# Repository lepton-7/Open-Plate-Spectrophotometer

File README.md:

# Open-Plate-Spectrophotometer

An open-source project to build a 96-well spectrophotometer operating at 620nm. Designed from the ground-up focusing on robust electronic design. Funded by the [think[box] Student Project Fund](https://case.edu/thinkbox/funding/student-project-fund) for the 2022-2023 academic year.

## Test Prototype (v0.0.2)

This project was born out of an appreciation for [Cerillo's portable microplate reader](https://cerillo.bio/stratus-2/) and the arrogant desire to open-source it by recreating what they made on my own. I designed a limited test prototype during the summer (I think sometime in July?) before the school year restarted to see what is required to realise the idea of a small form-factor, portable plate reader.

### Concept and Schematic

#### Functional block diagram

The idea is simple: control 96-element grids of LEDs and light sensors to address individual wells in a plate, convert the signal from the light sensor into something machine parsable, then finally do some ✨math✨ to get an optical density value for each well.

#### LED and detector grids

I decided to _not_ build a full 96-capable prototype. Instead, I opted to test all the relevant units I needed on a smaller scale. The result was a prototype with all 8 rows (A-H) but only two columns.

Independent control of each element is easily achieved by connecting the grid high and low sides to control MOSFETs:

Each row was connected to +5V via p-ch FETs (yes i know, they're wired incorrectly) and each column was connected to GND via n-ch FETs. Each FET gate is assigned its own pin on the MCU to independently control individual elements.

A similar idea is used for switching inputs from specific photodiode elements.

#### Detectors: photodiodes vs phototransistors

The hard bit for a device like this taking light that passes through the sample wells and converting that into a digital signal. Initially, I planned on using [phototransistors](https://www.digikey.com/en/articles/the-basics-of-photodiodes-and-phototransistors-and-how-to-apply-them) to transform a change in incident light intensity into a change in current. But these devices are pretty imprecise and do not have the best linearity. To make phototransistors work, I would have needed to do some really careful biasing -- something I did not think I needed.

The alternative was to use photodiodes. These are a bit better in the sense that they would have required a lot fewer supporting components. They also have pretty nice characteristics:

<fig>

<figcaption>Plot from Analog ADI</figcaption>
</fig>

These devices are pretty much linear in their response to incident light intensity: A 10x increase in incident intensity results in a 10x increase in reverse current.

#### Transimpedance amplifiers and ADCs

Converting current going through a photodiode into digital information is a two-step process. This is nothing new; the typical strategy is to use a transimpedance amplifier to convert transform a current signal into a voltage signal followed by an ADC that can convert the voltage signal into a digital value:

<fig>

<figcaption>TIA diagram from wikimedia commons.</figcaption>
</fig>

The transfer function is also pretty simple for a TIA:
$$ V_{out} = -I_{in}R_f $$

This is implemented as:

<fig>

</fig>

The principle is the same, just compressed a little. The current source is replaced by the photodiode, mulit-channel opamps are used to save space, and $V_{out}$ passes through a standard Schottky diode before being connected to the ADC inputs.

I used an 8ch ADC to independently connect each row for pseudo-switching of the detector outputs. High-side p-ch FET switches control V<sub>cc</sub> for the TIAs.

<fig>

</fig>

The 12-bit ADC converts output voltage into a digital signal referenced to a stable 5V signal generated by a voltage reference amplified by a low-noise voltage follower:

<fig>

</fig>

The MCU, an arduino nano, communicates with the ADC over I<sup>2</sup>C.

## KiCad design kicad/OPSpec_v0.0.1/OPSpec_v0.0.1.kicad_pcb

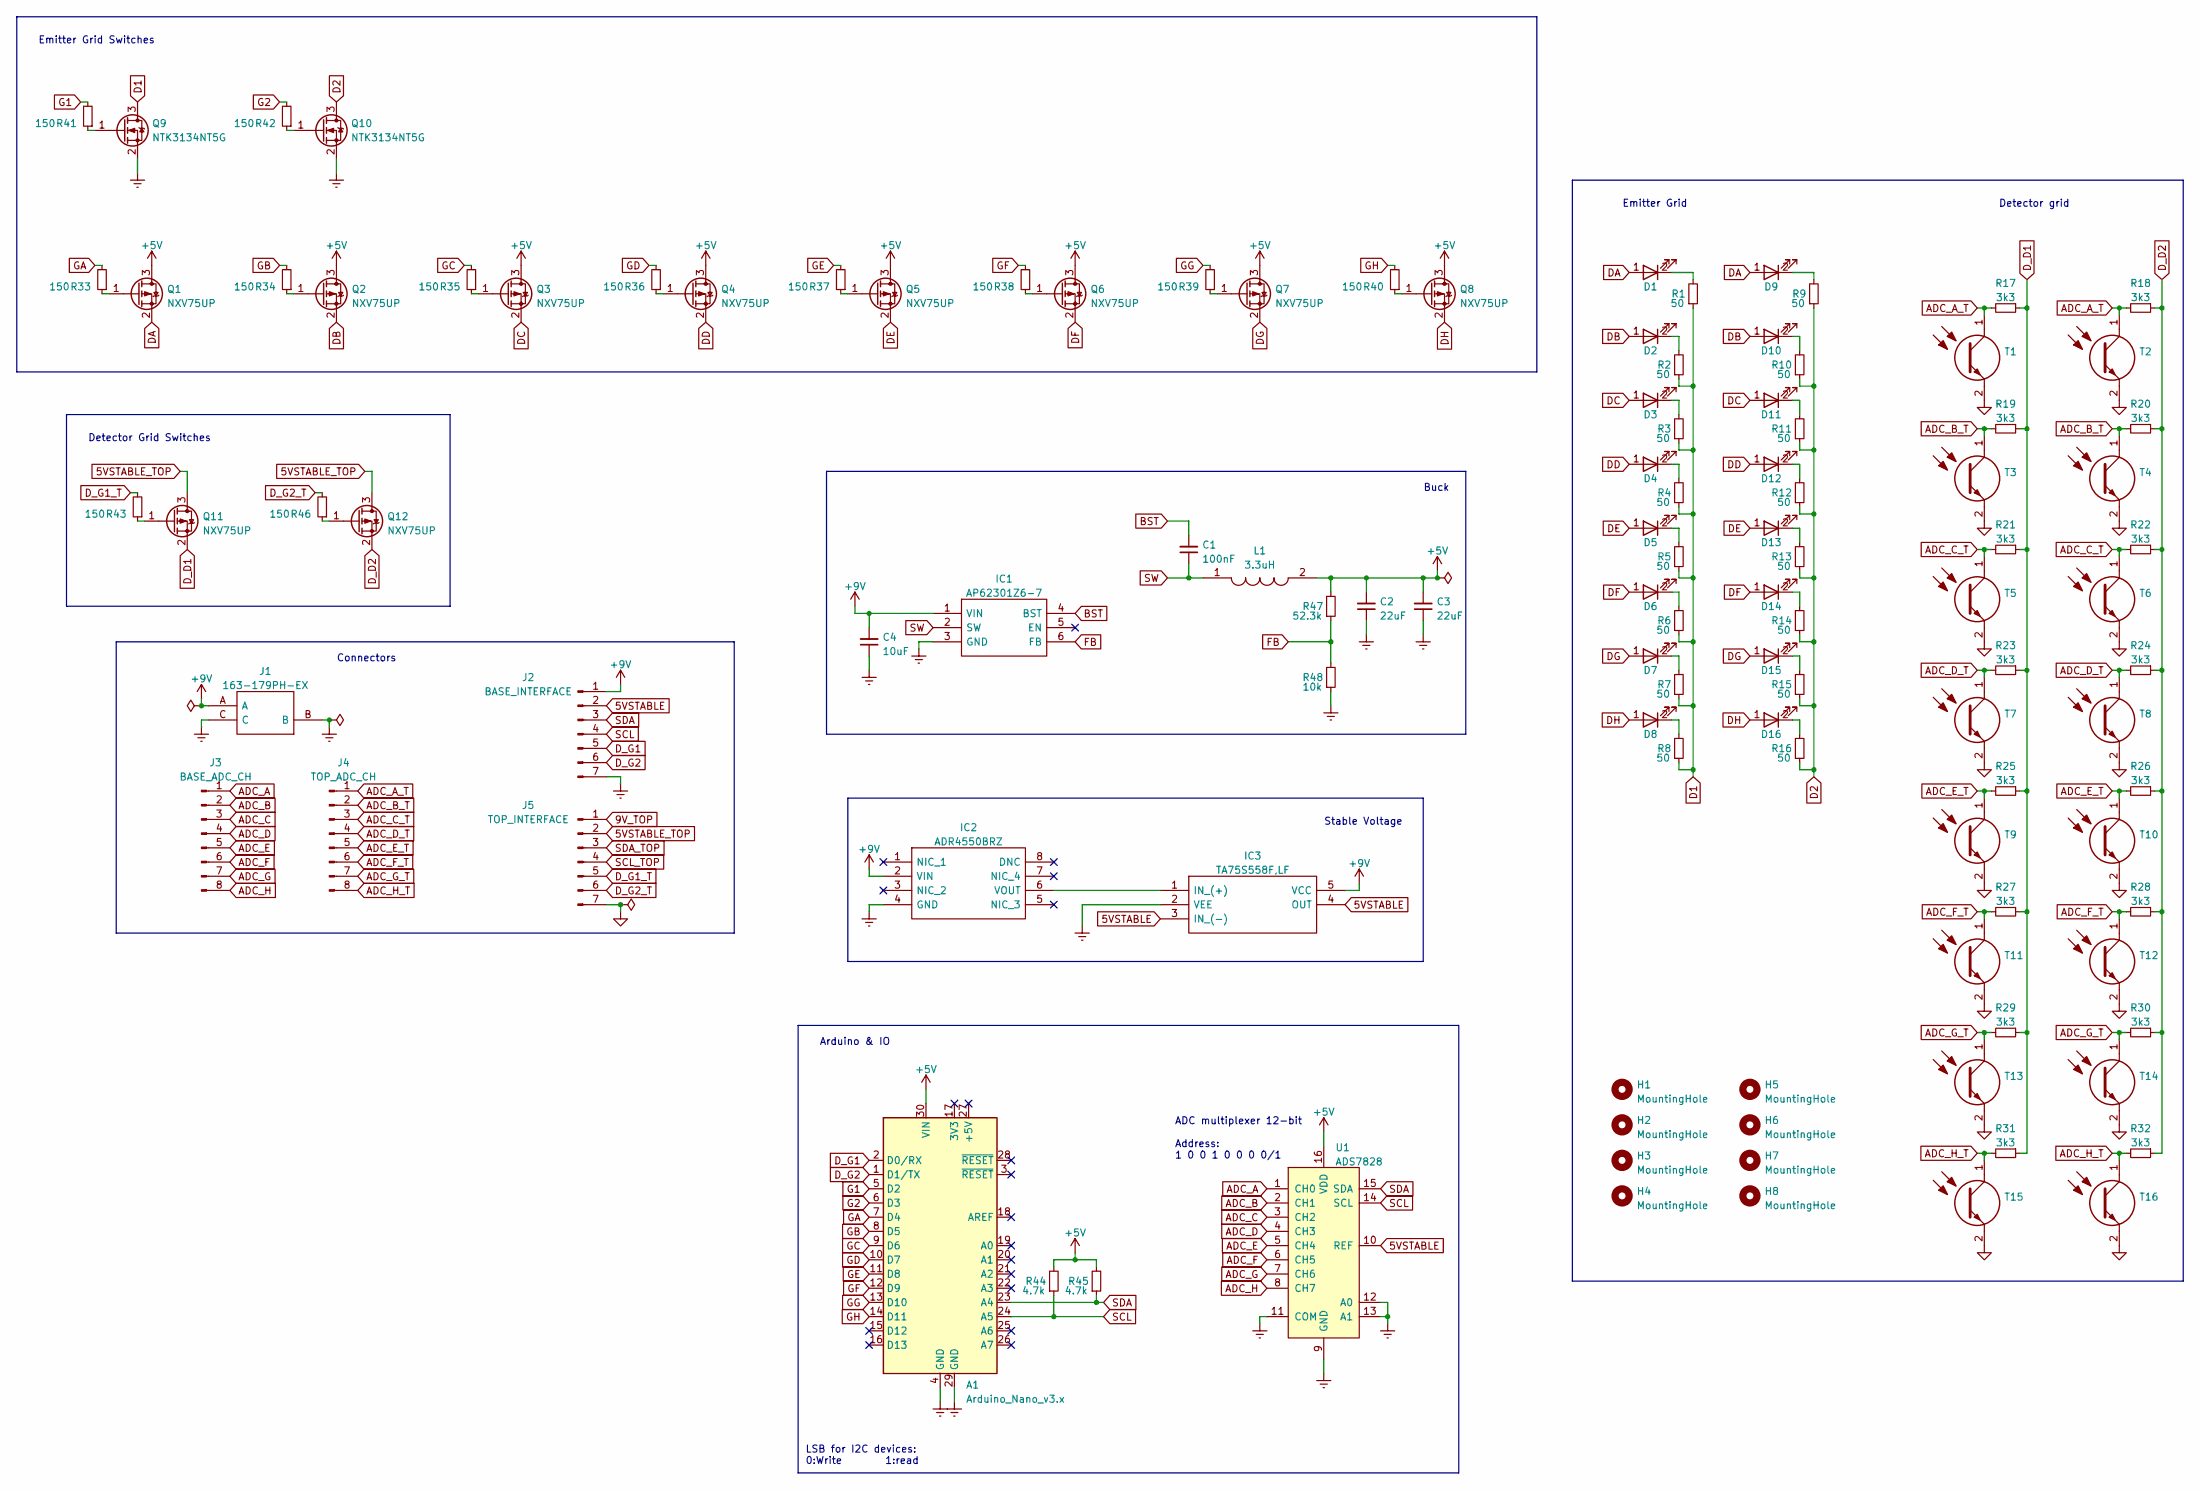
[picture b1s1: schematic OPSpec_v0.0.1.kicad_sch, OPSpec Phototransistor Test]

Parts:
A1: Arduino_Nano_v3.x; Arduino_Nano
C1: 100nF; C_0805_2012Metric
C2, C3: 22uF; C_0805_2012Metric
C4: 10uF; C_0805_2012Metric
D1, D2, D3, D4, D5, D6, D7, D8, D9, D10, D11, D12, D13, D14, D15, D16: GR_JTLPS1.23-G7H4-45-1-150-R33; GRJTLPS123G7H4451150R33; Mouser Part Number 720-GRJTLPS123A1052
H1, H2, H3, H4, H5, H6, H7, H8: MountingHole; MountingHole_2.5mm
IC1: AP62301Z6-7; SOTFL50P162X60-6N; Mouser Part Number 621-AP62301Z6-7
IC2: ADR4550BRZ; SOIC127P600X175-8N; Mouser Part Number 584-ADR4550BRZ
IC3: TA75S558F,LF; TA75S558FLF; Mouser Part Number 757-TA75S558FLF
J1: 163-179PH-EX; 163179PHEX; Mouser Part Number 163-179PH-EX
J2: BASE_INTERFACE; PinHeader_1x07_P2.54mm_Vertical
J3: BASE_ADC_CH; PinHeader_1x08_P2.54mm_Vertical
J4: TOP_ADC_CH; PinHeader_1x08_P2.54mm_Vertical
J5: TOP_INTERFACE; PinHeader_1x07_P2.54mm_Vertical
L1: 3.3uH; INDPM2016X100N; Mouser Part Number 963-MAKK2016T3R3M
Q1, Q2, Q3, Q4, Q5, Q6, Q7, Q8, Q11, Q12: NXV75UP; SOT-23
Q9, Q10: NTK3134NT5G; Mouser Part Number 863-NTK3134NT5G
R1, R2, R3, R4, R5, R6, R7, R8, R9, R10, R11, R12, R13, R14, R15, R16: 50; R_0603_1608Metric
R17, R18, R19, R20, R21, R22, R23, R24, R25, R26, R27, R28, R29, R30, R31, R32: 3k3; R_0603_1608Metric
R33, R34, R35, R36, R37, R38, R39, R40, R41, R42, R43, R46: 150; R_0603_1608Metric
R44, R45: 4.7k; R_0603_1608Metric
R47: 52.3k; R_0603_1608Metric
R48: 10k; R_0603_1608Metric
T1, T2, T3, T4, T5, T6, T7, T8, T9, T10, T11, T12, T13, T14, T15, T16: KDT00030TR; Mouser Part Number 512-KDT00030TR
U1: ADS7828; TSSOP-16_4.4x5mm_P0.65mm

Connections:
5VSTABLE: IC3.3 (IN_(-)), IC3.4 (OUT), J2.2, U1.10 (REF)
5VSTABLE_TOP: J5.2, Q11.3 (D), Q12.3 (D)
9V_TOP: J5.1
+5V: A1.30 (VIN), C2.2, C3.2, L1.2, Q1.3 (D), Q2.3 (D), Q3.3 (D), Q4.3 (D), Q5.3 (D), Q6.3 (D), Q7.3 (D), Q8.3 (D), R44.2, R45.2, R47.2, U1.16 (VDD)
+9V: C4.2, IC1.1 (VIN), IC2.2 (VIN), IC3.5 (VCC), J1.A, J2.1
ADC_A: J3.1, U1.1 (CH0)
ADC_A_T: J4.1, R17.2, R18.2, T1.1 (C), T2.1 (C)
ADC_B: J3.2, U1.2 (CH1)
ADC_B_T: J4.2, R19.2, R20.2, T3.1 (C), T4.1 (C)
ADC_C: J3.3, U1.3 (CH2)
ADC_C_T: J4.3, R21.2, R22.2, T5.1 (C), T6.1 (C)
ADC_D: J3.4, U1.4 (CH3)
ADC_D_T: J4.4, R23.2, R24.2, T7.1 (C), T8.1 (C)
ADC_E: J3.5, U1.5 (CH4)
ADC_E_T: J4.5, R25.2, R26.2, T9.1 (C), T10.1 (C)
ADC_F: J3.6, U1.6 (CH5)
ADC_F_T: J4.6, R27.2, R28.2, T11.1 (C), T12.1 (C)
ADC_G: J3.7, U1.7 (CH6)
ADC_G_T: J4.7, R29.2, R30.2, T13.1 (C), T14.1 (C)
ADC_H: J3.8, U1.8 (CH7)
ADC_H_T: J4.8, R31.2, R32.2, T15.1 (C), T16.1 (C)
BST: C1.2, IC1.4 (BST)
D1: Q9.3 (D), R1.1, R2.1, R3.1, R4.1, R5.1, R6.1, R7.1, R8.1
D2: Q10.3 (D), R9.1, R10.1, R11.1, R12.1, R13.1, R14.1, R15.1, R16.1
DA: D1.1 (A), D9.1 (A), Q1.2 (S)
DB: D2.1 (A), D10.1 (A), Q2.2 (S)
DC: D3.1 (A), D11.1 (A), Q3.2 (S)
DD: D4.1 (A), D12.1 (A), Q4.2 (S)
DE: D5.1 (A), D13.1 (A), Q5.2 (S)
DF: D6.1 (A), D14.1 (A), Q6.2 (S)
DG: D7.1 (A), D15.1 (A), Q7.2 (S)
DH: D8.1 (A), D16.1 (A), Q8.2 (S)
D_D1: Q11.2 (S), R17.1, R19.1, R21.1, R23.1, R25.1, R27.1, R29.1, R31.1
D_D2: Q12.2 (S), R18.1, R20.1, R22.1, R24.1, R26.1, R28.1, R30.1, R32.1
D_G1: A1.2 (D0/RX), J2.5
D_G1_T: J5.5, R43.2
D_G2: A1.1 (D1/TX), J2.6
D_G2_T: J5.6, R46.2
Earth: A1.4 (GND), A1.29 (GND), C2.1, C3.1, C4.1, IC1.3 (GND), IC2.4 (GND), IC3.2 (VEE), J1.B, J1.C, J2.7, Q9.2 (S), Q10.2 (S), R48.1, U1.9 (GND), U1.11 (COM), U1.12 (A0), U1.13 (A1)
FB: IC1.6 (FB), R47.1, R48.2
G1: A1.5 (D2), R41.2
G2: A1.6 (D3), R42.2
GA: A1.7 (D4), R33.2
GB: A1.8 (D5), R34.2
GC: A1.9 (D6), R35.2
GD: A1.10 (D7), R36.2
GE: A1.11 (D8), R37.2
GF: A1.12 (D9), R38.2
GG: A1.13 (D10), R39.2
GH: A1.14 (D11), R40.2
GND: J5.7, T1.2 (E), T2.2 (E), T3.2 (E), T4.2 (E), T5.2 (E), T6.2 (E), T7.2 (E), T8.2 (E), T9.2 (E), T10.2 (E), T11.2 (E), T12.2 (E), T13.2 (E), T14.2 (E), T15.2 (E), T16.2 (E)
unnamed: D1.2 (K), R1.2
unnamed: D2.2 (K), R2.2
unnamed: D3.2 (K), R3.2
unnamed: D4.2 (K), R4.2
unnamed: D5.2 (K), R5.2
unnamed: D6.2 (K), R6.2
unnamed: D7.2 (K), R7.2
unnamed: D8.2 (K), R8.2
unnamed: D9.2 (K), R9.2
unnamed: D10.2 (K), R10.2
unnamed: D11.2 (K), R11.2
unnamed: D12.2 (K), R12.2
unnamed: D13.2 (K), R13.2
unnamed: D14.2 (K), R14.2
unnamed: D15.2 (K), R15.2
unnamed: D16.2 (K), R16.2
unnamed: IC2.6 (VOUT), IC3.1 (IN_(+))
unnamed: Q1.1 (G), R33.1
unnamed: Q2.1 (G), R34.1
unnamed: Q3.1 (G), R35.1
unnamed: Q4.1 (G), R36.1
unnamed: Q5.1 (G), R37.1
unnamed: Q6.1 (G), R38.1
unnamed: Q7.1 (G), R39.1
unnamed: Q8.1 (G), R40.1
unnamed: Q9.1 (G), R41.1
unnamed: Q10.1 (G), R42.1
unnamed: Q11.1 (G), R43.1
unnamed: Q12.1 (G), R46.1
SCL: A1.24 (A5), J2.4, R44.1, U1.14 (SCL)
SCL_TOP: J5.4
SDA: A1.23 (A4), J2.3, R45.1, U1.15 (SDA)
SDA_TOP: J5.3
SW: C1.1, IC1.2 (SW), L1.1

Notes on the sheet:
ADC multiplexer 12-bit Address: 1 0 0 1 0 0 0 0/1
Arduino & IO
Connectors
Detector Grid Switches
Emitter Grid Switches
Detector grid
Buck
LSB for I2C devices: 0:Write 1:read
Emitter Grid
Stable Voltage

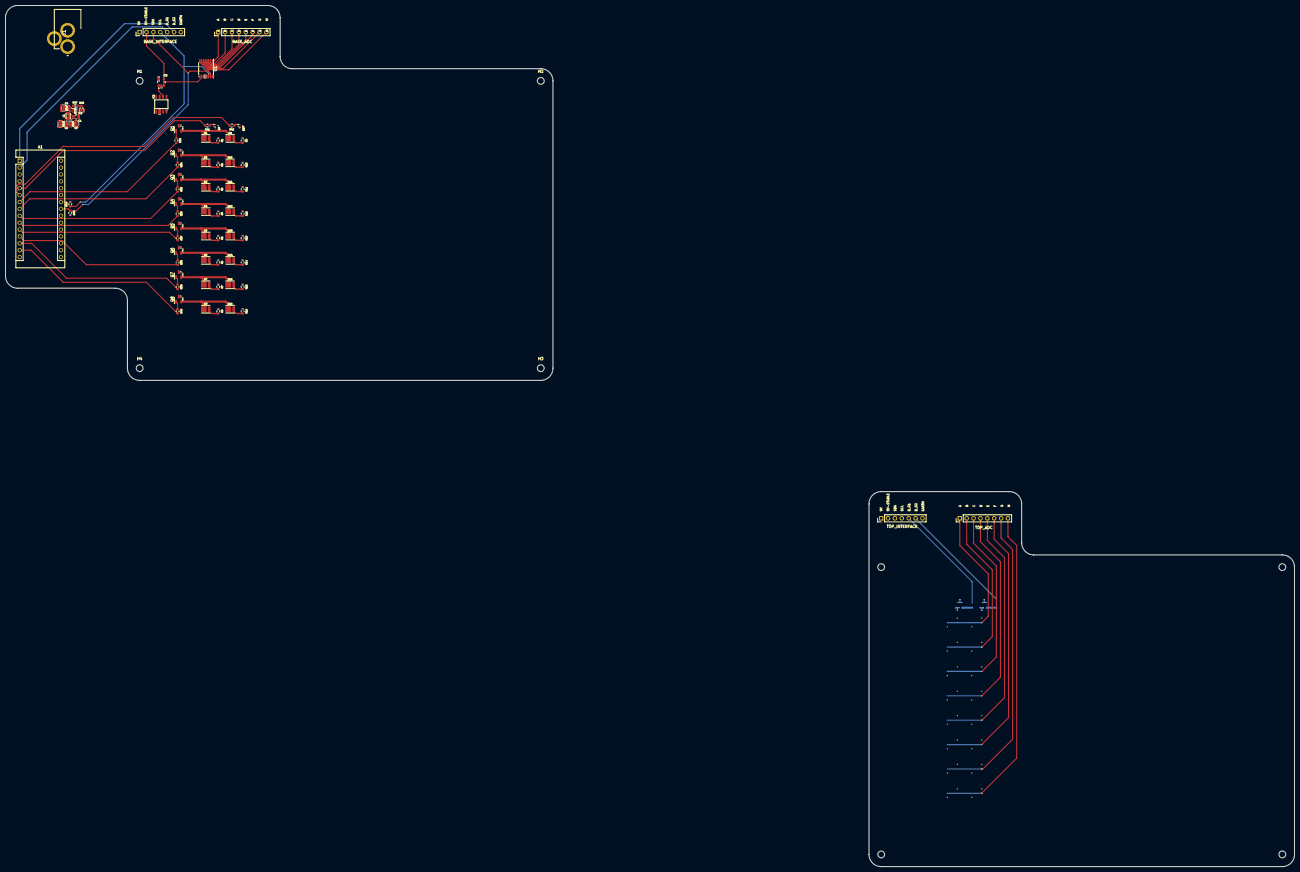
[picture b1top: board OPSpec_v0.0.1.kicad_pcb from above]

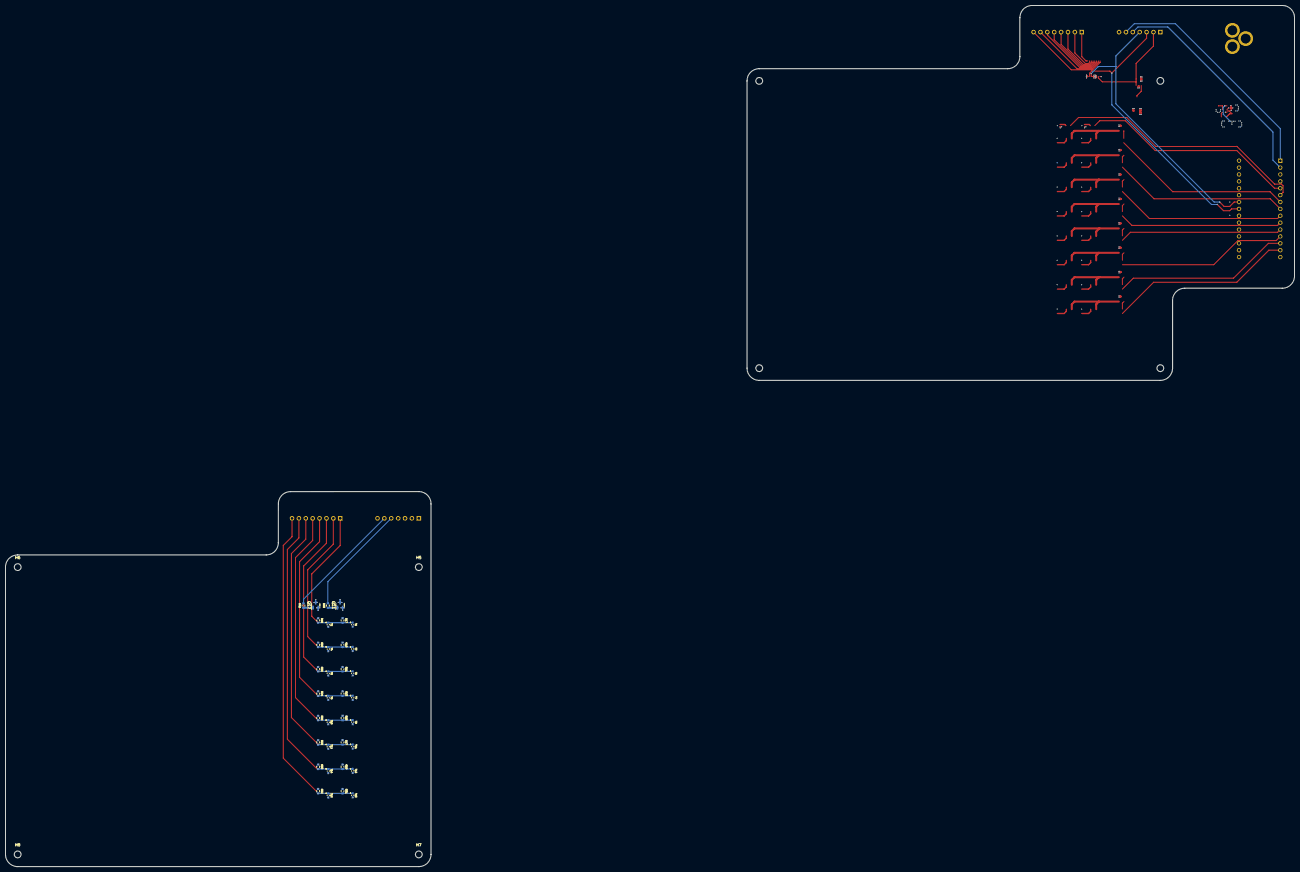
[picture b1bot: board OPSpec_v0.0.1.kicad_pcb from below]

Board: 4 copper layers, 475.6 x 317.7 mm, 115 parts (40 on the bottom side), 82 nets.

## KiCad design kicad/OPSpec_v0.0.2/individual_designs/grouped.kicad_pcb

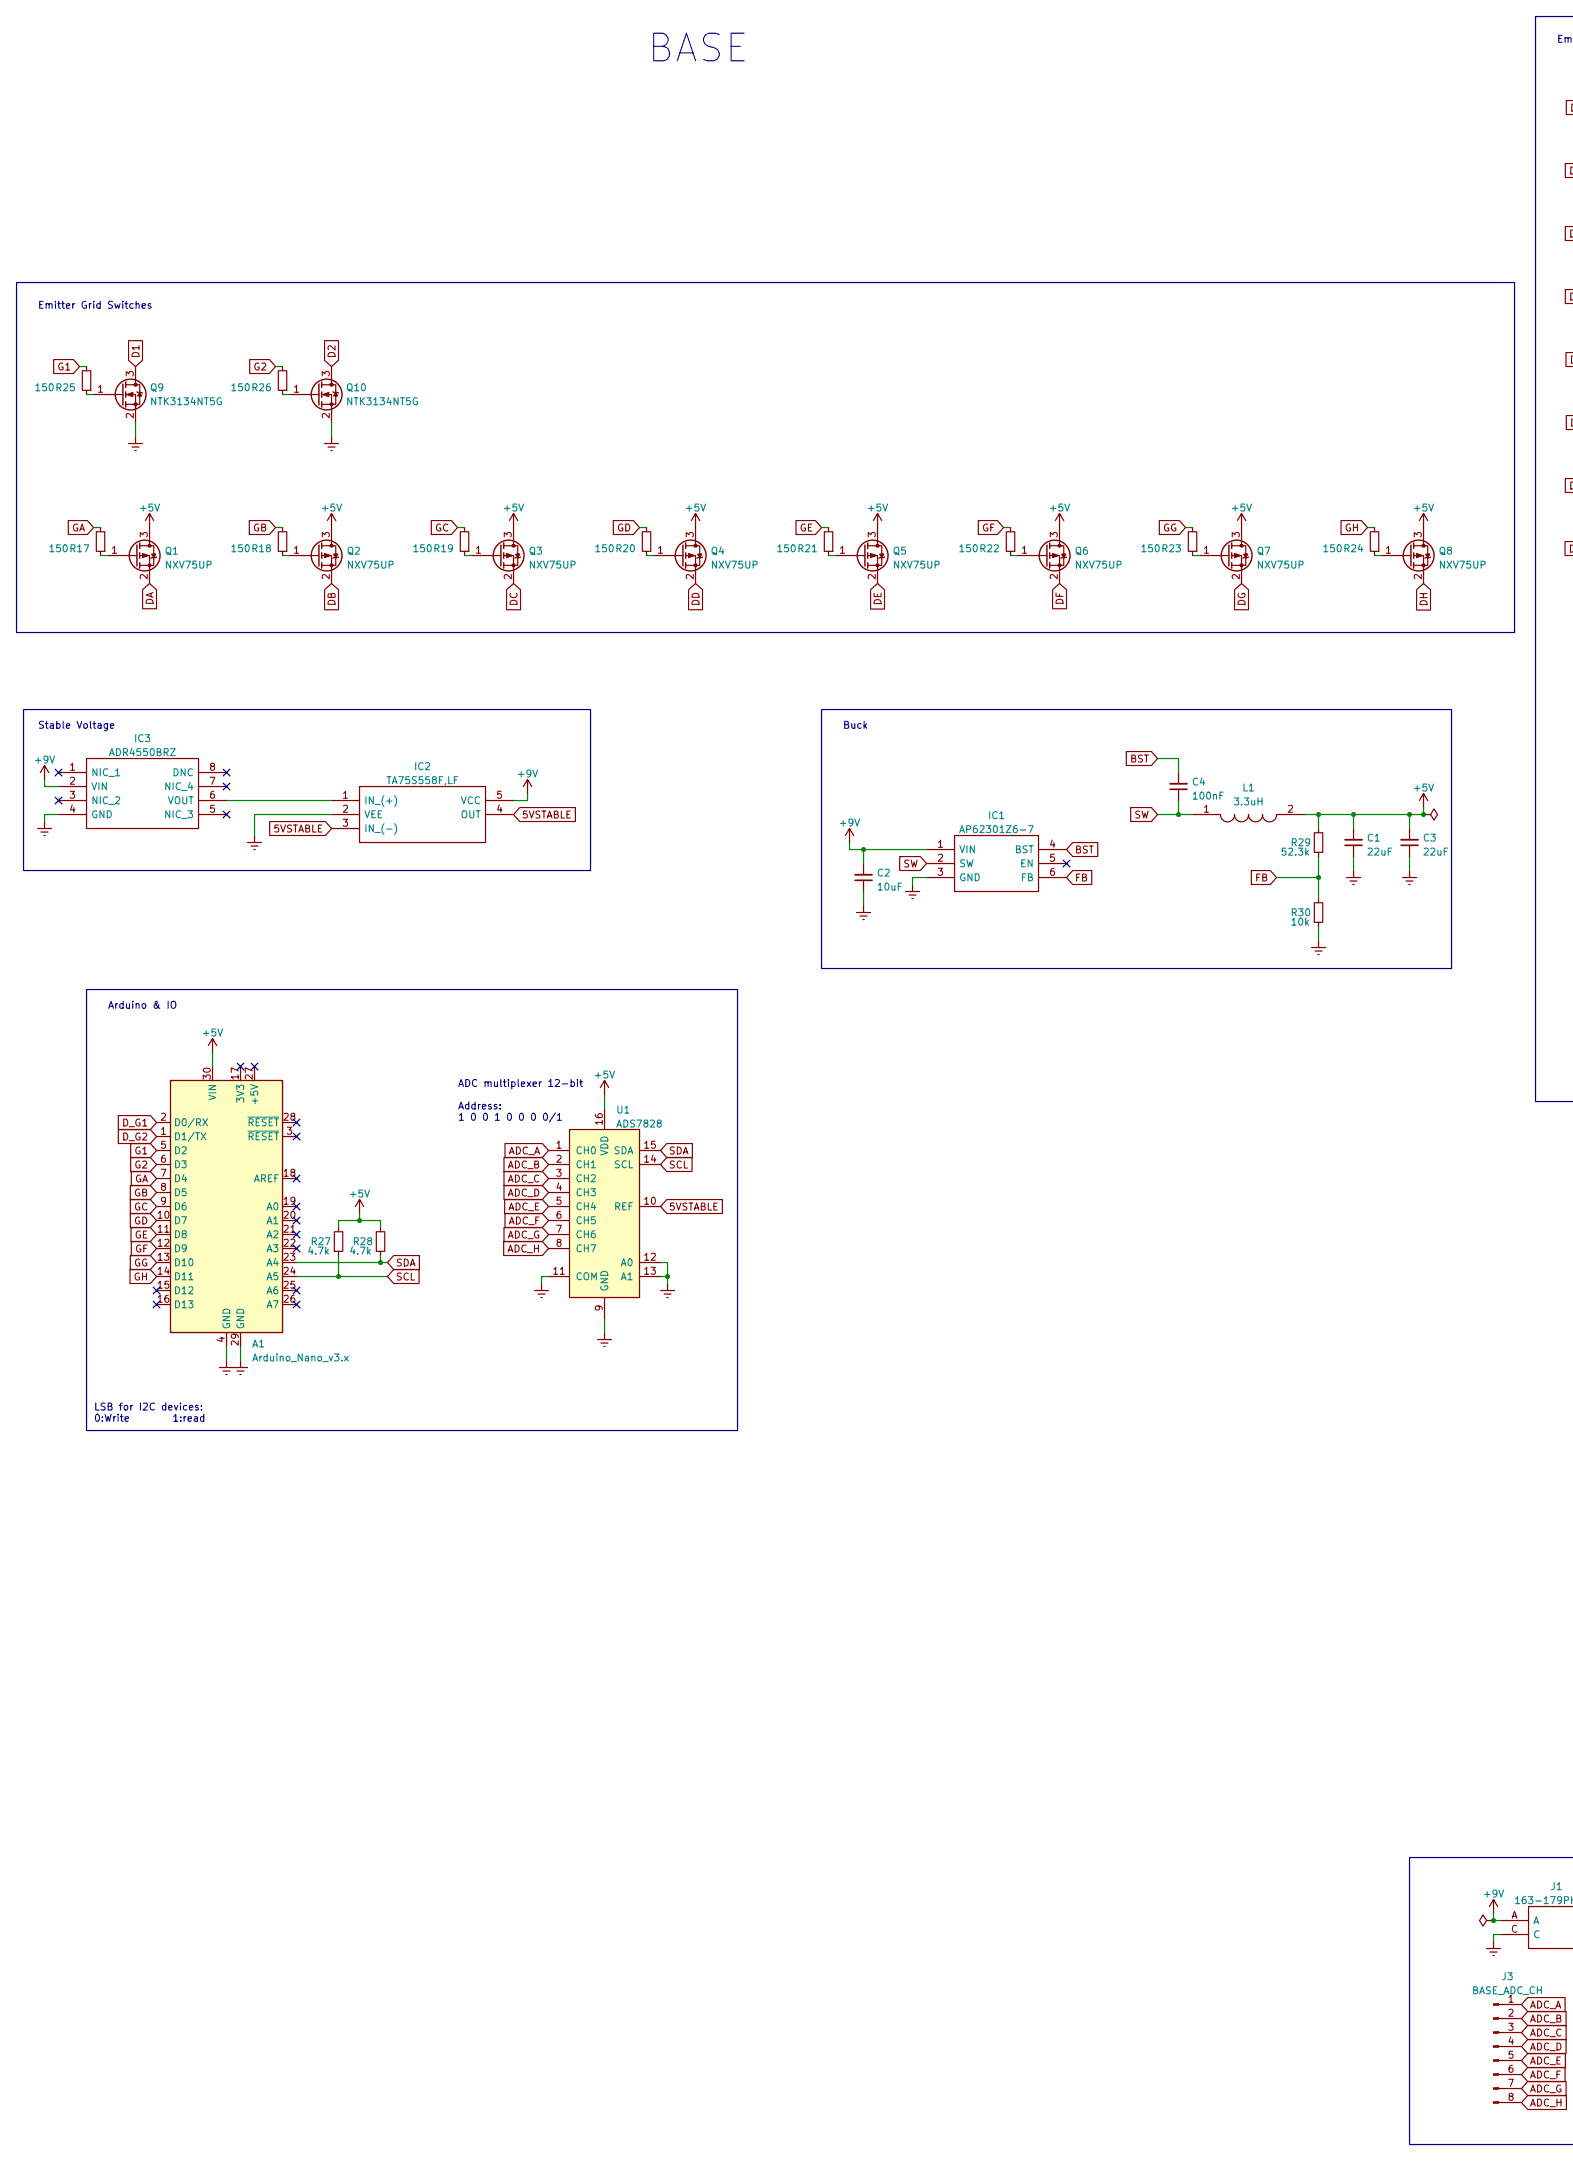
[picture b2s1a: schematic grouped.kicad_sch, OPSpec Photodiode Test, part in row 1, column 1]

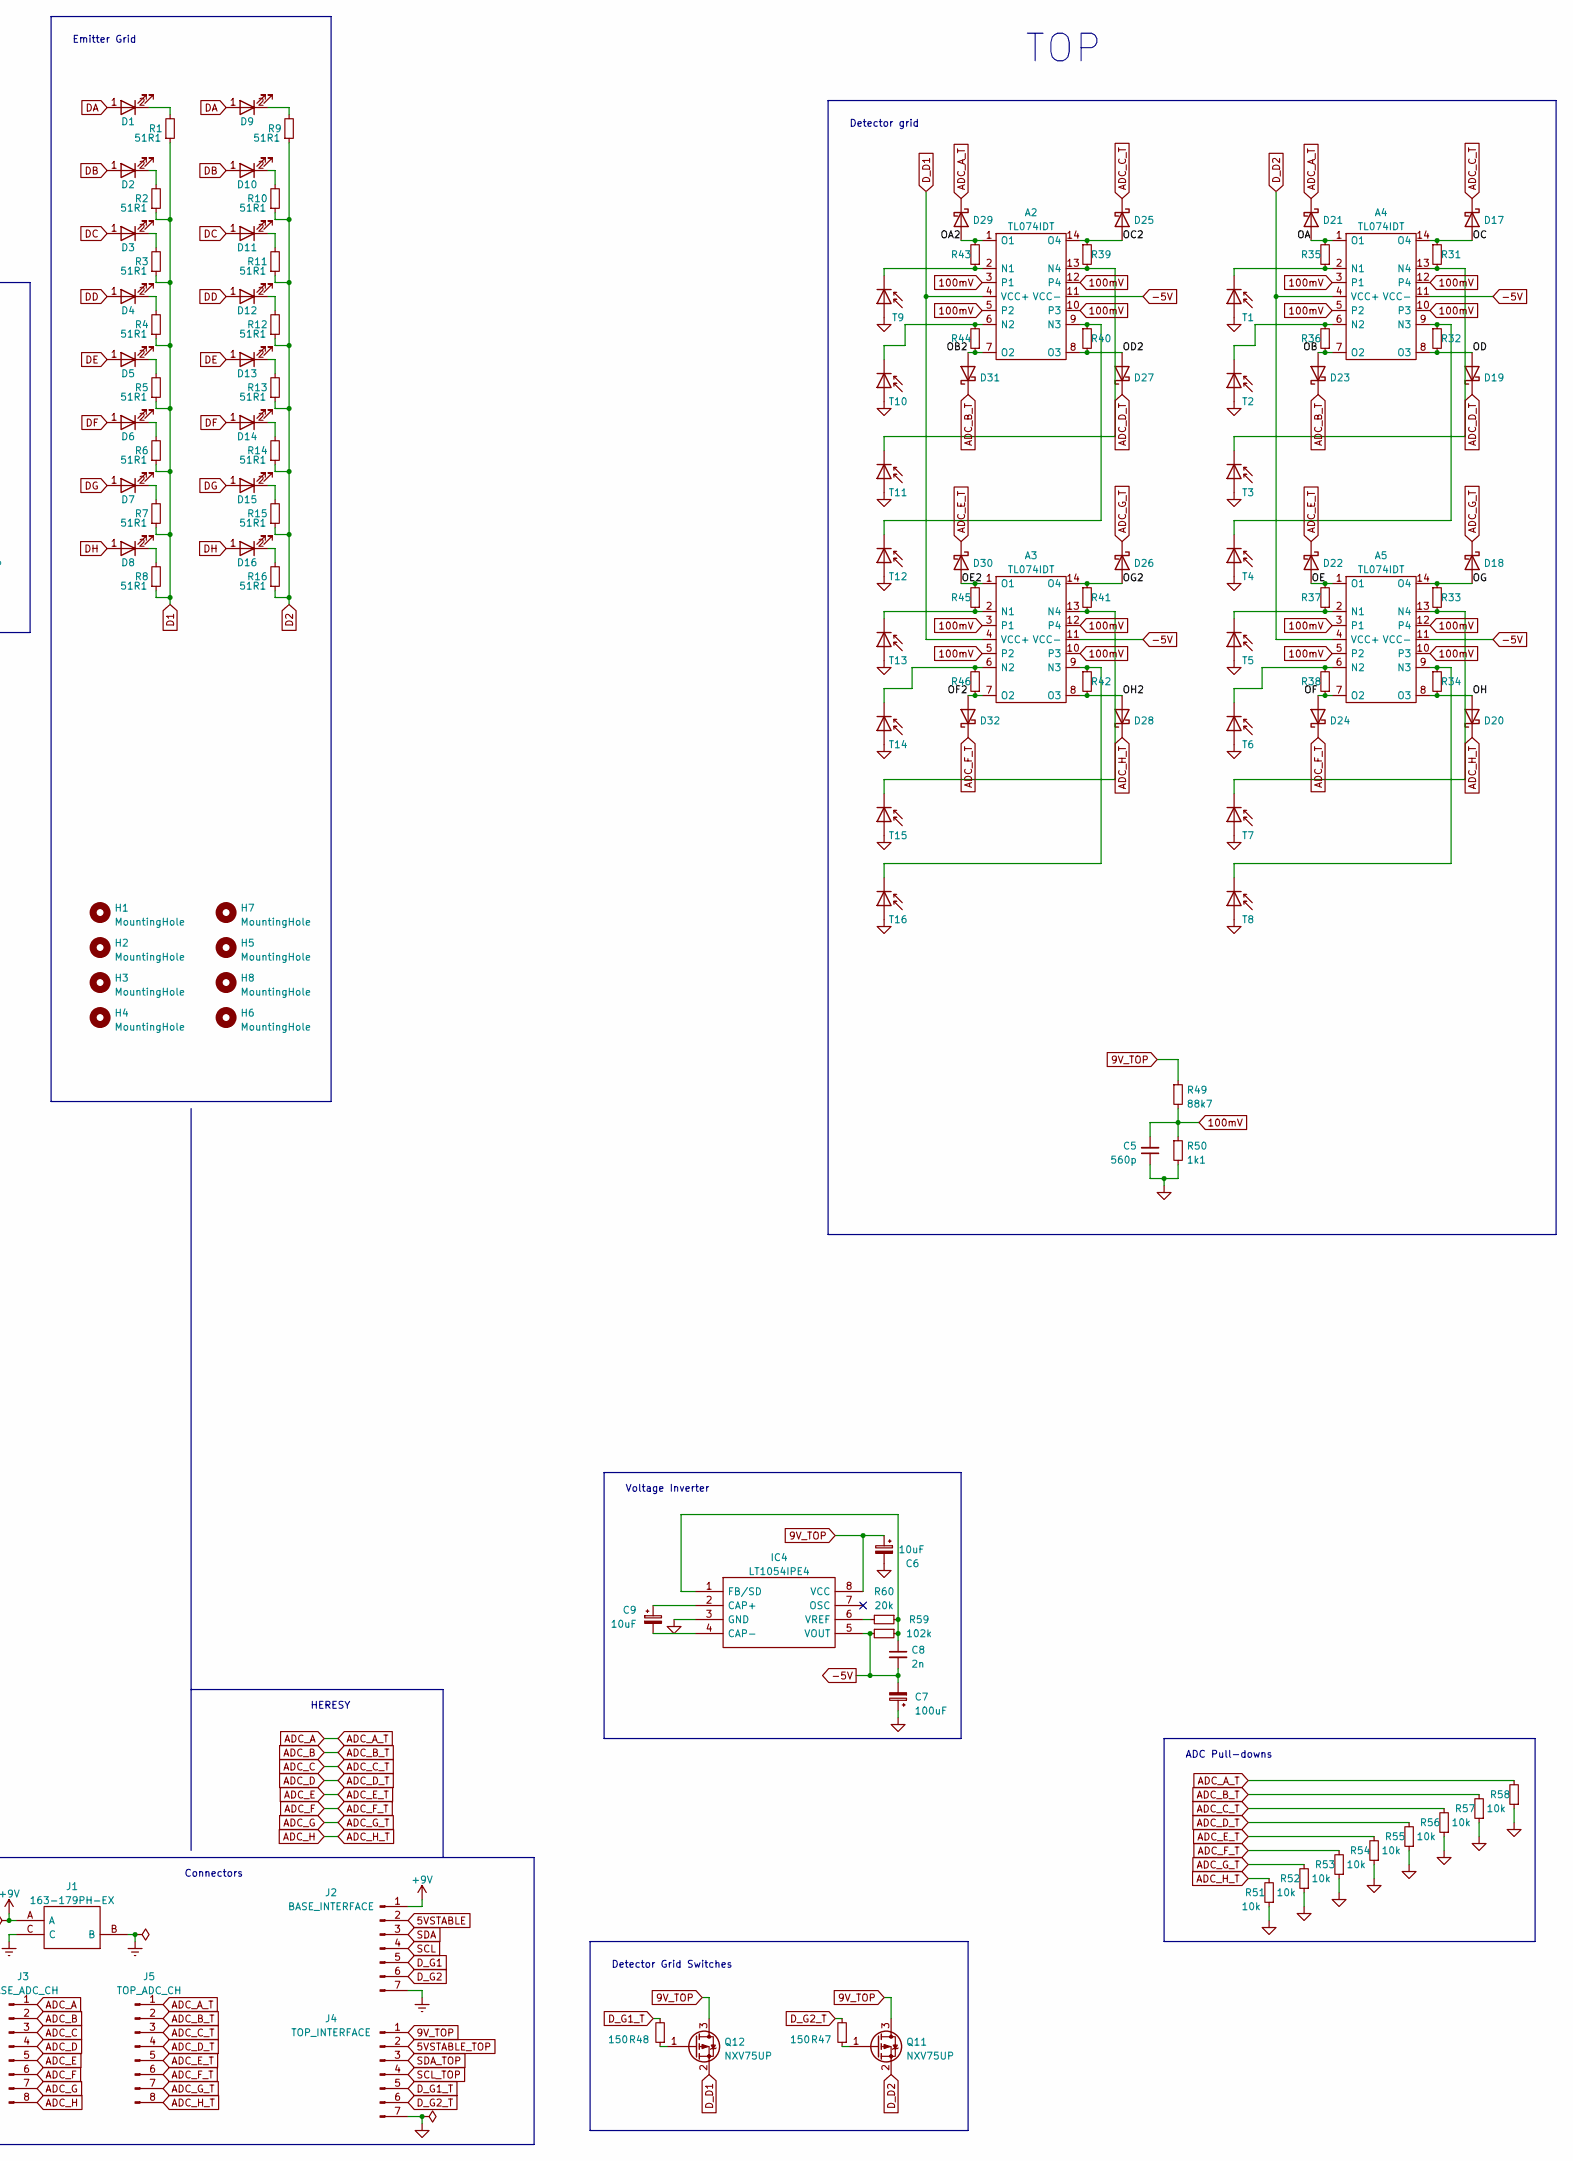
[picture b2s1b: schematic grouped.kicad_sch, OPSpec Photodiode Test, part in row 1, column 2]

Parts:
A1: Arduino_Nano_v3.x; Arduino_Nano
A2, A3, A4, A5: TL074IDT; SOIC127P600X175-14N; Mouser Part Number 511-TL074IDT
C1, C3: 22uF; C_0805_2012Metric
C2: 10uF; C_0805_2012Metric
C4: 100nF; C_0805_2012Metric
C5: 560p; C_0805_2012Metric
C6, C9: 10uF; CP_EIA-3216-10_Kemet-I
C7: 100uF; CP_EIA-6032-15_Kemet-U
C8: 2n; C_0805_2012Metric
D1, D2, D3, D4, D5, D6, D7, D8, D9, D10, D11, D12, D13, D14, D15, D16: GR_JTLPS1.23-G7H4-45-1-150-R33; GRJTLPS123G7H4451150R33; Mouser Part Number 720-GRJTLPS123A1052
D17, D18, D19, D20, D21, D22, D23, D24, D25, D26, D27, D28, D29, D30, D31, D32: RB521S30T5G; SODFL1608X70N; Mouser Part Number 863-RB521S30T5G
H1, H2, H3, H4, H5, H6, H7, H8: MountingHole; MountingHole_2.5mm
IC1: AP62301Z6-7; SOTFL50P162X60-6N; Mouser Part Number 621-AP62301Z6-7
IC2: TA75S558F,LF; TA75S558FLF; Mouser Part Number 757-TA75S558FLF
IC3: ADR4550BRZ; SOIC127P600X175-8N; Mouser Part Number 584-ADR4550BRZ
IC4: LT1054IPE4; DIP794W53P254L959H508Q8N; Mouser Part Number 595-LT1054IPE4
J1: 163-179PH-EX; 163179PHEX; Mouser Part Number 163-179PH-EX
J2: BASE_INTERFACE; PinHeader_1x07_P2.54mm_Vertical
J3: BASE_ADC_CH; PinHeader_1x08_P2.54mm_Vertical
J4: TOP_INTERFACE; PinHeader_1x07_P2.54mm_Vertical
J5: TOP_ADC_CH; PinHeader_1x08_P2.54mm_Vertical
L1: 3.3uH; INDPM2016X100N; Mouser Part Number 963-MAKK2016T3R3M
Q1, Q2, Q3, Q4, Q5, Q6, Q7, Q8, Q11, Q12: NXV75UP; SOT-23
Q9, Q10: NTK3134NT5G; Mouser Part Number 863-NTK3134NT5G
R1, R2, R3, R4, R5, R6, R7, R8, R9, R10, R11, R12, R13, R14, R15, R16: 51R1; R_0603_1608Metric
R17, R18, R19, R20, R21, R22, R23, R24, R25, R26, R47, R48: 150; R_0603_1608Metric
R27, R28: 4.7k; R_0603_1608Metric
R29: 52.3k; R_0603_1608Metric
R30, R51, R52, R53, R54, R55, R56, R57, R58: 10k; R_0603_1608Metric
R31, R32, R33, R34, R35, R36, R37, R38, R39, R40, R41, R42, R43, R44, R45, R46: 2M55; R_0603_1608Metric
R49: 88k7; R_0603_1608Metric
R50: 1k1; R_0603_1608Metric
R59: 102k; R_0603_1608Metric
R60: 20k; R_0603_1608Metric
T1, T2, T3, T4, T5, T6, T7, T8, T9, T10, T11, T12, T13, T14, T15, T16: SFH2716 A01; SFH2716
U1: ADS7828; TSSOP-16_4.4x5mm_P0.65mm

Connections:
5VSTABLE: IC2.3 (IN_(-)), IC2.4 (OUT), J2.2, U1.10 (REF)
5VSTABLE_TOP: J4.2
9V_TOP: C6.1, IC4.8 (VCC), J4.1, Q11.3 (D), Q12.3 (D), R49.1
100mV: A2.3 (P1), A2.5 (P2), A2.10 (P3), A2.12 (P4), A3.3 (P1), A3.5 (P2), A3.10 (P3), A3.12 (P4), A4.3 (P1), A4.5 (P2), A4.10 (P3), A4.12 (P4), A5.3 (P1), A5.5 (P2), A5.10 (P3), A5.12 (P4), C5.2, R49.2, R50.1
+5V: A1.30 (VIN), C1.2, C3.2, L1.2, Q1.3 (D), Q2.3 (D), Q3.3 (D), Q4.3 (D), Q5.3 (D), Q6.3 (D), Q7.3 (D), Q8.3 (D), R27.2, R28.2, R29.2, U1.16 (VDD)
+9V: C2.2, IC1.1 (VIN), IC2.5 (VCC), IC3.2 (VIN), J1.A, J2.1
-5V: A2.11 (VCC-), A3.11 (VCC-), A4.11 (VCC-), A5.11 (VCC-), C7.2, C8.2, IC4.5 (VOUT), R59.2
/OA: A4.1 (O1), D21.2 (A), R35.2
/OA2: A2.1 (O1), D29.2 (A), R43.2
/OB: A4.7 (O2), D23.2 (A), R36.1
/OB2: A2.7 (O2), D31.2 (A), R44.1
/OC: A4.14 (O4), D17.2 (A), R31.1
/OC2: A2.14 (O4), D25.2 (A), R39.1
/OD: A4.8 (O3), D19.2 (A), R32.2
/OD2: A2.8 (O3), D27.2 (A), R40.2
/OE: A5.1 (O1), D22.2 (A), R37.2
/OE2: A3.1 (O1), D30.2 (A), R45.2
/OF: A5.7 (O2), D24.2 (A), R38.1
/OF2: A3.7 (O2), D32.2 (A), R46.1
/OG: A5.14 (O4), D18.2 (A), R33.1
/OG2: A3.14 (O4), D26.2 (A), R41.1
/OH: A5.8 (O3), D20.2 (A), R34.2
/OH2: A3.8 (O3), D28.2 (A), R42.2
ADC_A: D21.1 (K), D29.1 (K), J3.1, J5.1, R58.2, U1.1 (CH0)
ADC_B: D23.1 (K), D31.1 (K), J3.2, J5.2, R57.2, U1.2 (CH1)
ADC_C: D17.1 (K), D25.1 (K), J3.3, J5.3, R56.2, U1.3 (CH2)
ADC_D: D19.1 (K), D27.1 (K), J3.4, J5.4, R55.2, U1.4 (CH3)
ADC_E: D22.1 (K), D30.1 (K), J3.5, J5.5, R54.2, U1.5 (CH4)
ADC_F: D24.1 (K), D32.1 (K), J3.6, J5.6, R53.2, U1.6 (CH5)
ADC_G: D18.1 (K), D26.1 (K), J3.7, J5.7, R52.2, U1.7 (CH6)
ADC_H: D20.1 (K), D28.1 (K), J3.8, J5.8, R51.2, U1.8 (CH7)
BST: C4.2, IC1.4 (BST)
D1: Q9.3 (D), R1.1, R2.1, R3.1, R4.1, R5.1, R6.1, R7.1, R8.1
D2: Q10.3 (D), R9.1, R10.1, R11.1, R12.1, R13.1, R14.1, R15.1, R16.1
DA: D1.1 (A), D9.1 (A), Q1.2 (S)
DB: D2.1 (A), D10.1 (A), Q2.2 (S)
DC: D3.1 (A), D11.1 (A), Q3.2 (S)
DD: D4.1 (A), D12.1 (A), Q4.2 (S)
DE: D5.1 (A), D13.1 (A), Q5.2 (S)
DF: D6.1 (A), D14.1 (A), Q6.2 (S)
DG: D7.1 (A), D15.1 (A), Q7.2 (S)
DH: D8.1 (A), D16.1 (A), Q8.2 (S)
D_D1: A2.4 (VCC+), A3.4 (VCC+), Q12.2 (S)
D_D2: A4.4 (VCC+), A5.4 (VCC+), Q11.2 (S)
D_G1: A1.2 (D0/RX), J2.5
D_G1_T: J4.5, R48.2
D_G2: A1.1 (D1/TX), J2.6
D_G2_T: J4.6, R47.2
Earth: A1.4 (GND), A1.29 (GND), C1.1, C2.1, C3.1, IC1.3 (GND), IC2.2 (VEE), IC3.4 (GND), J1.B, J1.C, J2.7, Q9.2 (S), Q10.2 (S), R30.1, U1.9 (GND), U1.11 (COM), U1.12 (A0), U1.13 (A1)
FB: IC1.6 (FB), R29.1, R30.2
G1: A1.5 (D2), R25.2
G2: A1.6 (D3), R26.2
GA: A1.7 (D4), R17.2
GB: A1.8 (D5), R18.2
GC: A1.9 (D6), R19.2
GD: A1.10 (D7), R20.2
GE: A1.11 (D8), R21.2
GF: A1.12 (D9), R22.2
GG: A1.13 (D10), R23.2
GH: A1.14 (D11), R24.2
GND: C5.1, C6.2, C7.1, IC4.3 (GND), J4.7, R50.2, R51.1, R52.1, R53.1, R54.1, R55.1, R56.1, R57.1, R58.1, T1.1 (A), T2.1 (A), T3.1 (A), T4.1 (A), T5.1 (A), T6.1 (A), T7.1 (A), T8.1 (A), T9.1 (A), T10.1 (A), T11.1 (A), T12.1 (A), T13.1 (A), T14.1 (A), T15.1 (A), T16.1 (A)
unnamed: A2.2 (N1), R43.1, T9.2 (K)
unnamed: A2.6 (N2), R44.2, T10.2 (K)
unnamed: A2.9 (N3), R40.1, T12.2 (K)
unnamed: A2.13 (N4), R39.2, T11.2 (K)
unnamed: A3.2 (N1), R45.1, T13.2 (K)
unnamed: A3.6 (N2), R46.2, T14.2 (K)
unnamed: A3.9 (N3), R42.1, T16.2 (K)
unnamed: A3.13 (N4), R41.2, T15.2 (K)
unnamed: A4.2 (N1), R35.1, T1.2 (K)
unnamed: A4.6 (N2), R36.2, T2.2 (K)
unnamed: A4.9 (N3), R32.1, T4.2 (K)
unnamed: A4.13 (N4), R31.2, T3.2 (K)
unnamed: A5.2 (N1), R37.1, T5.2 (K)
unnamed: A5.6 (N2), R38.2, T6.2 (K)
unnamed: A5.9 (N3), R34.1, T8.2 (K)
unnamed: A5.13 (N4), R33.2, T7.2 (K)
unnamed: C8.1, IC4.1 (FB/SD), R59.1, R60.1
unnamed: C9.1, IC4.2 (CAP+)
unnamed: C9.2, IC4.4 (CAP-)
unnamed: D1.2 (K), R1.2
unnamed: D2.2 (K), R2.2
unnamed: D3.2 (K), R3.2
unnamed: D4.2 (K), R4.2
unnamed: D5.2 (K), R5.2
unnamed: D6.2 (K), R6.2
unnamed: D7.2 (K), R7.2
unnamed: D8.2 (K), R8.2
unnamed: D9.2 (K), R9.2
unnamed: D10.2 (K), R10.2
unnamed: D11.2 (K), R11.2
unnamed: D12.2 (K), R12.2
unnamed: D13.2 (K), R13.2
unnamed: D14.2 (K), R14.2
unnamed: D15.2 (K), R15.2
unnamed: D16.2 (K), R16.2
unnamed: IC2.1 (IN_(+)), IC3.6 (VOUT)
unnamed: IC4.6 (VREF), R60.2
unnamed: Q1.1 (G), R17.1
unnamed: Q2.1 (G), R18.1
unnamed: Q3.1 (G), R19.1
unnamed: Q4.1 (G), R20.1
unnamed: Q5.1 (G), R21.1
unnamed: Q6.1 (G), R22.1
unnamed: Q7.1 (G), R23.1
unnamed: Q8.1 (G), R24.1
unnamed: Q9.1 (G), R25.1
unnamed: Q10.1 (G), R26.1
unnamed: Q11.1 (G), R47.1
unnamed: Q12.1 (G), R48.1
SCL: A1.24 (A5), J2.4, R27.1, U1.14 (SCL)
SCL_TOP: J4.4
SDA: A1.23 (A4), J2.3, R28.1, U1.15 (SDA)
SDA_TOP: J4.3
SW: C4.1, IC1.2 (SW), L1.1

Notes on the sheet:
ADC multiplexer 12-bit Address: 1 0 0 1 0 0 0 0/1
Arduino & IO
HERESY
Connectors
ADC Pull-downs
Detector Grid Switches
Emitter Grid Switches
Detector grid
TOP
BASE
Buck
Voltage Inverter
LSB for I2C devices: 0:Write 1:read
Emitter Grid
Stable Voltage
